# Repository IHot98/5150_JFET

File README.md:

# 5150 JFET
---
Ne realizirani projekt 

5150 jfet je gitarski efekt pedala koja simulira zvuk lampaškog pojačala peavy 5150

Dizajnirana shema i pločica u KiCadu 

Projekt je nedovršen i zaboravljen zbog viših sila fakulteta. XD  

Zadnji put rađeno na projektu davne 2017 godine.

Neke slike
---
[shema](https://github.com/IHot98/5150_JFET/blob/main/Screenshot_1.png)

[PCB 1](https://github.com/IHot98/5150_JFET/blob/main/Screenshot_2.png)

[PCB 2](https://github.com/IHot98/5150_JFET/blob/main/Screenshot_3.png)

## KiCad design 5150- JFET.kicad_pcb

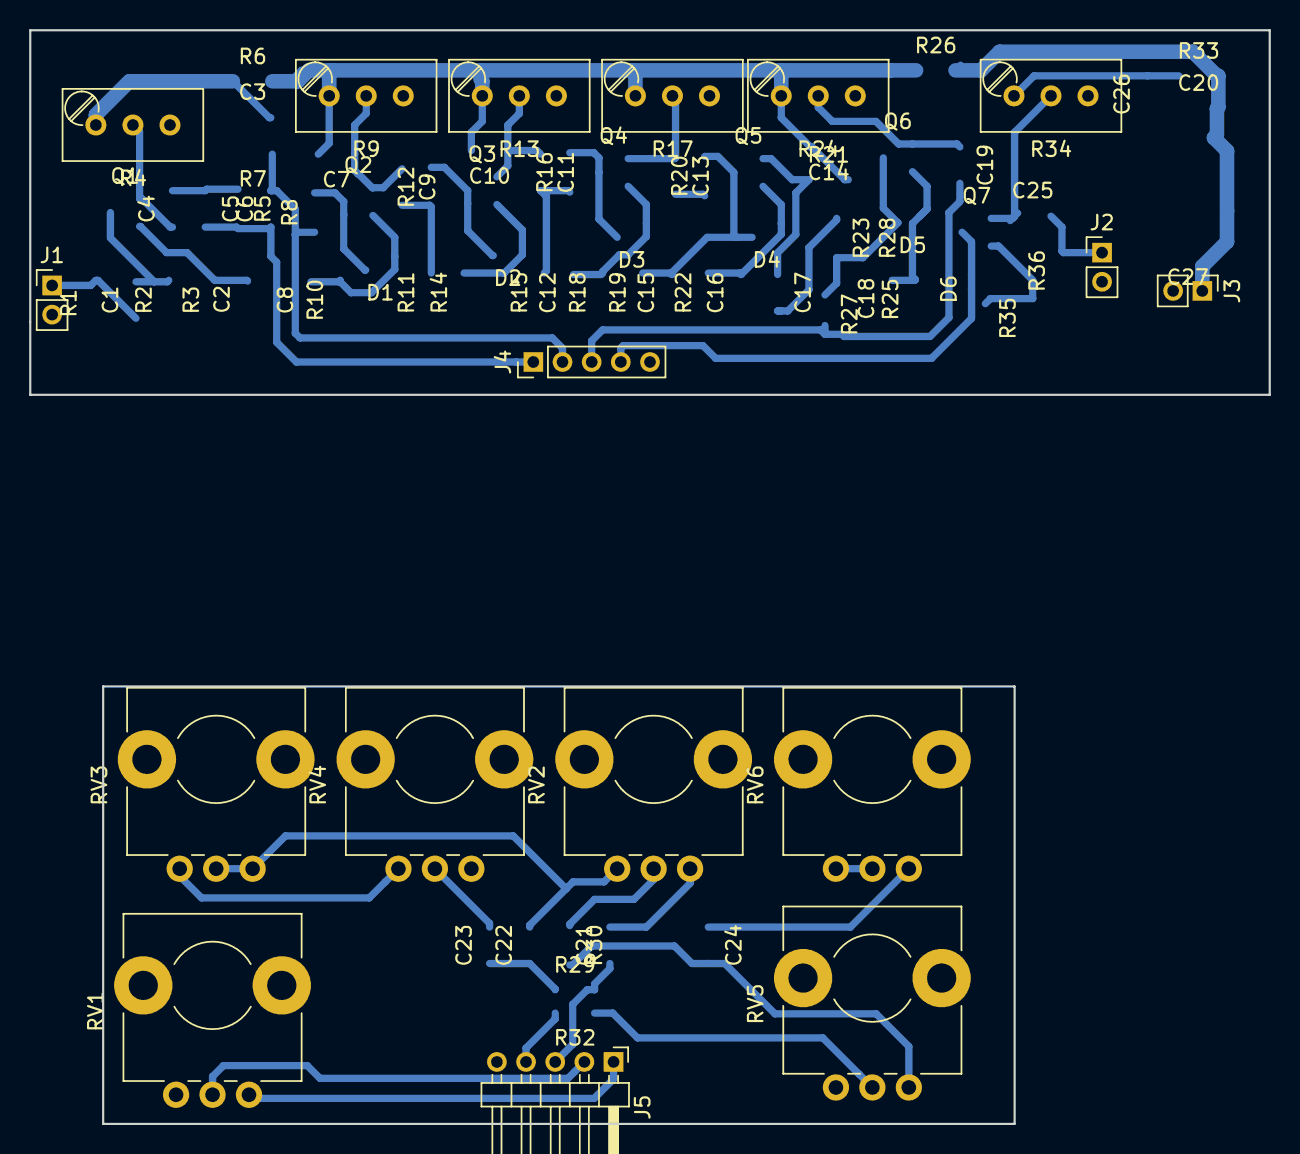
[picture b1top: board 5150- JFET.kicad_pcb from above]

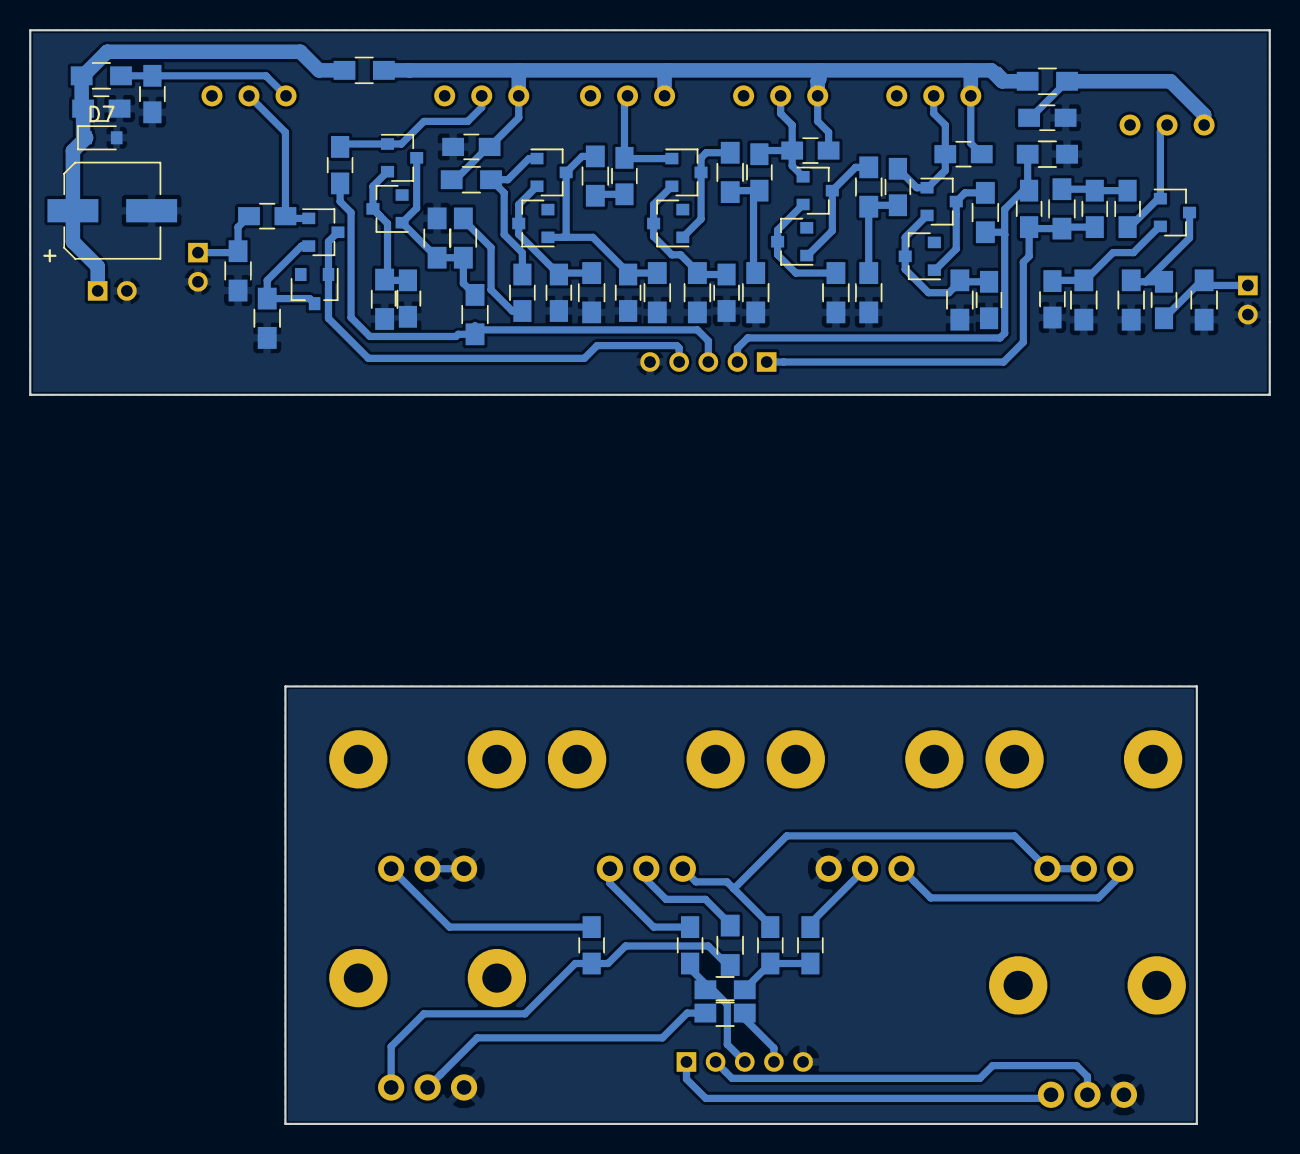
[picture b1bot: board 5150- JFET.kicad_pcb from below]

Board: 2 copper layers, 85.0 x 75.0 mm, 87 parts (70 on the bottom side), 50 nets.

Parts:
C1, C2, C3, C4, C5, C6, C7, C8, C9, C10, C11, C12, C13, C14, C15, C16, C17, C18, C19, C20, C21, C22, C23, C24, C25, C26: C; C_0805_HandSoldering
C27: CP; CP_Elec_6.3x5.3
D1, D2, D3, D4, D5, D6: D_ALT; D_SOT-23_ANK
D7: D_ALT; D_0805
J1, J2, J3: Conn_01x02; Pin_Header_Straight_1x02_Pitch2.00mm
J4: Conn_01x05_Female; Socket_Strip_Straight_1x05_Pitch2.00mm
J5: Conn_01x05_Male; Pin_Header_Angled_1x05_Pitch2.00mm
Q1, Q2, Q3, Q4, Q5, Q6, Q7: Q_NJFET_DSG; SOT-23
R1, R2, R3, R5, R6, R7, R8, R10, R11, R12, R14, R15, R16, R18, R19, R20, R21, R22, R23, R25, R26, R27, R28, R29, R30, R32, R33, R35, R36: R; R_0805_HandSoldering
R4, R9, R13, R17, R24, R34: RTRIM; Potentiometer_Trimmer_Bourns_3296W
RV1: POT; Potentiometer_Alps_RK09L_Sleve_Single_Horizontal
RV2: treble; Potentiometer_Alps_RK09L_Sleve_Single_Horizontal
RV3: bass; Potentiometer_Alps_RK09L_Sleve_Single_Horizontal
RV4: mid; Potentiometer_Alps_RK09L_Sleve_Single_Horizontal
RV5: level; Potentiometer_Alps_RK09L_Sleve_Single_Horizontal
RV6: hi; Potentiometer_Alps_RK09L_Sleve_Single_Horizontal

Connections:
/EQin: C19.1, J4.3, R27.1
/EQout: D6.2, J4.4, Q7.3
/GainPin1: C5.1, C6.2, J4.1, R5.1
/GainPin2: C6.1, J4.2, R7.2, R8.2
GND: C2.2, C3.2, C8.2, C12.2, C14.2, C15.2, C16.2, C18.2, C20.2, C26.2, C27.2, D7.2, J1.2, J2.2, J3.2, J4.5, R1.2, R2.2, R3.2, R7.1, R10.2, R11.2, R14.2, R15.2, R18.2, R19.2, R22.2, R25.2, R28.2, R35.2, R36.2
GNDA: J5.5, RV1.3, RV4.1, RV5.3, RV6.2, RV6.3
unnamed: C1.1, Q1.3, R2.1
unnamed: C2.1, Q1.2, R3.1
unnamed: C3.1, R4.1, R6.2
unnamed: C4.1, C5.2, R5.2
unnamed: C4.2, Q1.1, R4.2
unnamed: C7.2, C9.2, Q2.1, R9.2
unnamed: C8.1, D1.1, Q2.2, R10.1
unnamed: C9.1, R11.1, R12.2
unnamed: C7.1, C10.1, C14.1, R6.1, R9.1, R13.1, R17.1, R21.1, R24.1, R26.2
unnamed: C10.2, C11.2, Q3.1, R13.2
unnamed: C11.1, R15.1, R16.2
unnamed: C12.1, D3.1, Q4.2, R18.1
unnamed: C13.1, R20.2
unnamed: C13.2, Q4.1, R17.2
unnamed: C15.1, D4.2, Q5.3, R19.1, R20.1
unnamed: C16.1, D4.1, Q5.2, R22.1
unnamed: C17.1, R23.2
unnamed: C17.2, Q5.1, R21.2
unnamed: C18.1, D5.1, Q6.2, R25.1
unnamed: C19.2, Q6.1, R24.2
unnamed: C21.1, RV2.1
unnamed: C21.2, J5.3, R29.1
unnamed: C22.1, RV2.3, RV3.1, RV3.2
unnamed: C22.2, C23.2, R29.2
unnamed: C23.1, RV4.2
unnamed: C24.1, R30.1, RV5.1
unnamed: C24.2, RV6.1
unnamed: C25.2, Q7.1, R34.2
unnamed: C26.1, R33.2, R34.1
unnamed: D1.2, Q2.3, R8.1
unnamed: D2.1, Q3.2, R14.1
unnamed: D2.2, Q3.3, R12.1
unnamed: D3.2, Q4.3, R16.1
unnamed: D5.2, Q6.3, R23.1, R27.2, R28.1
unnamed: D6.1, Q7.2, R35.1
unnamed: J5.1, RV1.1
unnamed: J5.2, RV1.2
unnamed: J5.4, R32.1
unnamed: R30.2, RV2.2
unnamed: R32.2, RV5.2
unnamed: RV3.3, RV4.3
input: C1.2, J1.1, R1.1
output: C25.1, J2.1, R36.1
power: C20.1, C27.1, D7.1, J3.1, R26.1, R33.1

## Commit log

2021-07-12 final
